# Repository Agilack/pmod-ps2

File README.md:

PS/2 interface PMOD
===================

This project is a small circuit (PMOD form factor) that allow to connect and
control a PS/2 device using an UART. On the PMOD side, pinout and signals use
the Type 3A specifications (UART).

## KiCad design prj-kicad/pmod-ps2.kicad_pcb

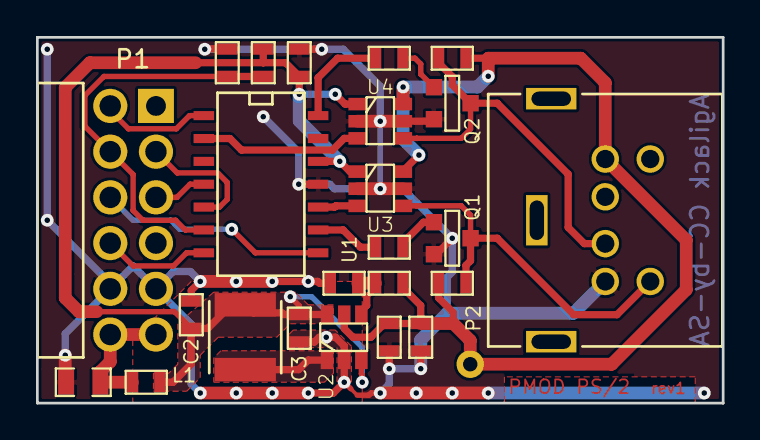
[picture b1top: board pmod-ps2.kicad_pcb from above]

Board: 2 copper layers, 38.1 x 20.3 mm, 25 parts (0 on the bottom side), 20 nets.

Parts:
C1: 10uF; SMD0805
C2, C3, C4, C5: 4,7uF; SMD0603
C6: 100nF; SMD0603
C7: 1uF; SMD0603
L1: FB100; SMD0603
L2: INDUCTOR; I_TYS4012
P1: PMOD; CONN_PMOD-Male
P2: CONN_PS_2; CONN-DIN6_4850261
Q1, Q2: BC846; SOT23-3
R1, R2: R; SMD0603
R3, R4: 4,7k; SMD0603
R5, R6, R7: 10k; SMD0603
TP2: CONN_1; TP
U1: ATSAMD09C13A; SOIC-14
U2: MCP1640; SOT23-6
U3, U4: SN74LVC1T45; SOT23-6

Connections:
+3.3V: C2.1, C3.1, C6.1, L1.2, L2.1, R7.2, U1.12, U2.3, U2.6, U3.1, U4.1
+5V: C4.1, C5.1, P2.4, R1.1, R3.1, R4.1, TP2.1, U2.5, U3.6, U4.6
/V_SW: L2.2, U2.1
CLK_I: U1.10, U3.3
CLK_O: R5.2, U1.9
DAT_I: U1.2, U4.3
DAT_O: R6.2, U1.14
GND: C1.2, C2.2, C3.2, C4.2, C5.2, C6.2, C7.2, P1.5, P1.11, P2.3, Q1.2, Q2.2, R2.2, U1.11, U2.2, U3.2, U3.5, U4.2, U4.5
IRQ: P1.7, U1.1
unnamed: P2.1, Q2.3, R4.2, U4.4
unnamed: P2.5, Q1.3, R3.2, U3.4
unnamed: Q1.1, R5.1
unnamed: Q2.1, R6.1
unnamed: R1.2, R2.1, U2.4
PMOD_RXD: P1.3, U1.4
PMOD_TXD: P1.2, U1.5
RST: C7.1, P1.8, R7.1, U1.6
SWCLK: P1.10, U1.7
SWDIO: P1.9, U1.8
VCC: C1.1, L1.1, P1.6, P1.12

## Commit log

2020-07-18 ADD: Insert initial schematics + routing for PS/2 pmod
2020-07-19 = ADD/ Create production files for rev1

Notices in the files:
prj-kicad/pmod-ps2.kicad_pcb:
License: CC-by-SA 2.0
Agilack CC-by-SA
